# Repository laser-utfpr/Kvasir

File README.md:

# Kvasir

   Dependencies:  
  
   -CMake 3.9

      for Ubuntu: (older version at the packages center atm) get it at: https://cmake.org/download/
      (if you have an older version it's advisable to unistall it first)  

      for Fedora: sudo dnf install cmake

   -OpenCV 2  

      for Ubuntu: sudo apt install libopencv-dev  

      for Fedora: sudo dnf install opencv-devel

   -Boost Libraries  

      for Ubuntu: sudo apt install libboost-all-dev

      for Fedora: sudo dnf install boost-devel

   -Qt5

      for Ubuntu: sudo apt install qttools5-dev

      for Fedora: sudo dnf install qt5-devel-5.11.1-3.fc28.noarch  

	If you want to use gpu, follow this instructions:
		https://www.learnopencv.com/install-opencv3-on-ubuntu/
		https://medium.com/@mengjiunchiou/build-opencv-caffe-with-cuda-9-0-on-ubuntu-16-04-b2794a41612d

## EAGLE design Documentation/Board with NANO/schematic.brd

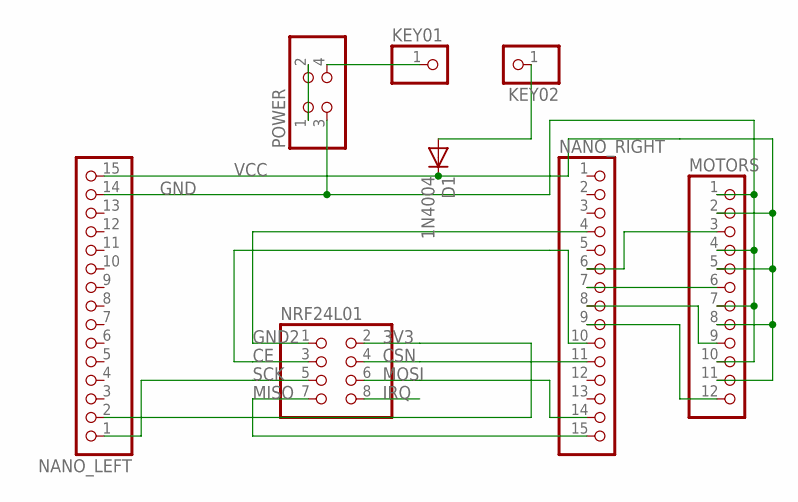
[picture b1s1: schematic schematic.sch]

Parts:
D1: 1N4004; DO41-10
KEY01, KEY02: PINHD-1X1; 1X01
MOTORS: PINHD-1X12; 1X12
NANO_LEFT: PINHD-1X15; 1X15
NANO_RIGHT: PINHD-1X15; 1X15
NRF24L01: PINHD-2X4; 2X04
POWER: PINHD-2X2; 2X02

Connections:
3V3: NANO_LEFT.2, NRF24L01.2
CE: NANO_RIGHT.10, NRF24L01.3
CSN: NANO_RIGHT.11, NRF24L01.4
GND: MOTORS.1, MOTORS.4, MOTORS.7, MOTORS.10, NANO_LEFT.14, POWER.3
GND2: NANO_RIGHT.4, NRF24L01.1
IRQ: NRF24L01.8
MISO: NANO_RIGHT.15, NRF24L01.7
MOSI: NANO_RIGHT.14, NRF24L01.6
unnamed: POWER.1, POWER.2
unnamed: KEY01.1, POWER.4
unnamed: D1.A, KEY02.1
unnamed: MOTORS.12, NANO_RIGHT.9
unnamed: MOTORS.9, NANO_RIGHT.8
unnamed: MOTORS.6, NANO_RIGHT.7
unnamed: MOTORS.3, NANO_RIGHT.6
SCK: NANO_LEFT.1, NRF24L01.5
VCC: D1.C, MOTORS.2, MOTORS.5, MOTORS.8, MOTORS.11, NANO_LEFT.15

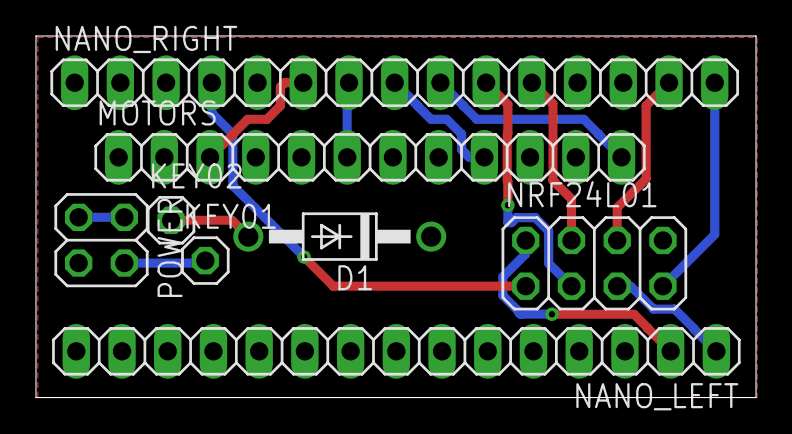
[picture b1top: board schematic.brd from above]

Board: 2 copper layers, 40.0 x 20.1 mm, 8 parts (0 on the bottom side), 16 nets.

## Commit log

2017-08-15 fixed mask opening
2017-08-15 object tracking implemented but not working
2017-08-21 lots of things working
2017-08-21 deleted some junk
2017-08-22 starting to make an interprocesser
2017-08-22 backup
2017-08-28 shared memory crashing often
2017-08-28 shared memory working
2017-08-29 working_with_shared_memory
2017-08-30 vision on cmake, starting obro
2017-08-30 deleting this
2017-08-30 little things
2017-09-05 trying to get obro working
2017-09-06 single shared memory writing, working across processes
2017-09-15 obro progressing
2017-09-18 little progress
2017-09-22 robots 1 and 2, working on 3
2017-09-25 3 robots, right angle ref
2017-09-26 function descriptions for obro
2017-09-26 doing all it needs to do for now
2017-09-27 some comments
2017-10-06 nao sei
2017-10-06 attemp to reorganize stuff
2017-10-06 attempt to reorganize stuff
2017-10-09 something, I don't even know
2017-10-09 some memory leak fix + AI skeleton
2017-10-10 readme dep instructions
2017-10-17 making the ai...
2017-10-19 ai progress?
2017-10-24 we won't back down
2017-10-25 slowly getting there
2017-10-26 now compiling, kbhit in a separate file
2017-10-27 ai progress + some configuring
2017-10-29 readme skipping lines fix
2017-10-30 ai stuff
2017-10-30 leetul
2017-11-01 calculate goalkeeper objective position
2017-11-06 we done?
2017-11-07 little mem leak fix
2017-11-08 kbhit fix, some other stuff
2017-11-08 fixes...
2017-11-08 constants set, no vel on robot 0, save us
2017-11-13 robots semi chasing the ball
2017-11-17 merging with bifrost and freebot
2018-02-05 starting new Kvasirgit checkout Kvasir2 !
2018-02-05 SMMCGUI
2018-02-05 building skeleton
2018-02-05 rebuild
2018-02-08 "qt test project and progress to compiling qt on cmake"
2018-02-15 fk u -fpic! now compiling qt5 with cmake
2018-02-15 now AUTO_MOC and AUTO_UIC are being bitches
2018-02-17 holy guacamole, it's compiling
2018-02-17 compiling with opencv and boost
2018-02-17 CMake 3.9 dependency updated at README
2018-02-19 actually programming now
2018-02-22 progress, using boost serialization now (being a bitch tho)
2018-02-23 boost serialization now included correctly (new boost installation at readme!)
2018-02-23 boost readme
2018-03-01 shared memory progress n keys
2018-03-01 liking signals slots, constructing some sm variables
2018-03-01 ideasNreminders update
2018-03-05 starting to add ai variables
2018-03-05 probaly finished sm variables, added mutex protection
2018-03-06 finishing smmc routines
2018-03-07 paths on settings file, some signals connected
2018-03-12 some initializations and signal to slot connections
2018-03-12 gonna try to use filesystem
2018-03-13 qcoreapplication app exe dir path
2018-03-14 making form
2018-03-14 some parameters changed, ui progress
2018-03-15 game tab finished(!?)
2018-03-19 real ui stuff being implemented
2018-03-19 progress on setting up the ui
2018-03-19 more tasty progress
2018-03-20 typo fix, starting other tabs
2018-03-20 different ally and enemy actions
2018-03-22 updating only on write detection
2018-03-27 vision settings ui
2018-03-27 starting identifiers menus, shutdown fixes
2018-03-28 progress as always
2018-03-29 tags menu and searched region working
2018-04-02 qtTest gone and ui almost finished
2018-04-02 fck forgot ball color (ai settings done tho), making signals
2018-04-03 missing ball button done, missing signals connected
2018-04-03 printing entities?
2018-04-04 printing entities and status
2018-04-04 game control image done (I hope)
2018-04-09 last opencv rectangle thingys
2018-04-10 little bug corrections and commenting
2018-04-10 bug fixes
2018-04-11 boost serialization fix, starting habrok
2018-04-11 makes SMMC read any .sp file
2018-04-12 file stuff, cout and instructions for SMMC
2018-04-16 habrok class
2018-04-17 SMMC without tests, progress in Habrok
2018-04-17 making smmclib
2018-04-18 habrok things
2018-04-18 habrok modeling
2018-04-19 some signal and slot stuff
2018-04-23 starts the image processing
2018-04-24 finds contours
2018-04-24 Habrok should be kinda working with SMMCGUI, but it seg faults
2018-04-25 found seg fault culprits
2018-05-15 just a test bro
2018-05-16 changes sm keys to boost interprocess strings on SMMCGUI
2018-05-16 Habrok opens boost interprocess keys, and working!
2018-05-22 SMMCGUI now compiles with supposedly working boost vectors and strings
2018-05-23 Habrok compiling but not working and giving seg faults
2018-06-12 my signal in your slot
2018-06-19 all habrok signals are not working!
2018-07-11 useless test stuff
2018-07-13 image not in shared memory anymore, commit before qthread adjustments
2018-07-16 making qthread tests
2018-10-12 somehow SMMCGUI threads seem to be working
2018-10-13 image data should be being passed correctly
2018-10-14 image through shared memory working!
2018-10-14 tests deleted
2018-10-14 readme updated for fedora
2018-10-14 Habrok calibration wip
2018-10-15 fedora actually showed a error and some warnings
2018-10-15 habrok contours removed, ui showing
2018-10-15 nothing at all
2018-10-19 habrok ui finished
2018-10-20 color menu working, still needs image menu programming
2018-10-21 image type menu and image displaying
2018-10-22 camera id box
2018-10-23 camera id opening working
2018-10-23 loading camera id at initialization
2018-10-24 makes communication module Vard
2018-10-25 Fixes file loading
2018-10-25 Fixes modules not loading
2018-10-26 scrolls variable accesso 4 lines down, fixing bug
2018-10-26 fixed keys from memory for communication
2018-10-30 part of the changes to match kvasir2 commit
2018-10-30 fixing commit
2018-10-30 fixing commit.
2018-10-30 fixing commit..
2018-10-30 fixing commit...
2018-10-31 fixes habrok calibration loading, starting robot recognizer
2018-11-01 finding ball, other entities wip
2018-11-02 finds robot1
2018-11-02 moar things on calibration, robot4
2018-11-03 habrok should be done o/
2018-11-03 slight aesthetic fix
2018-11-03 fix for opencv3.0
2018-11-03 starting vor
2018-11-03 some bugs fixes, vor communicating, strategy wip
2018-11-04 turbo -O3 compiling
2018-11-04 not tested and missing stuff but should have a simple playing capability
2018-11-05 slight fix, -O3 breaks things in some PCs
2018-11-06 fixes
2018-11-08 removed some pointers
2018-11-09 things
2018-12-18 stopped the use of unnecessary pointers
2018-12-18 reused some pointers, because without them the motor doesn't answer correctly
2019-01-22 start documentation
2019-01-22 start Vard documentation
2019-01-23 finished vard documentation
2019-01-24 Include hardware documentation
2019-02-12 updated class diagrams
2019-02-12 update class diagrams
2019-02-13 made Habrok class diagram, start the SMMCGUI one
2019-02-14 fineshed class diagrams
2019-02-15 started the new vard program
2019-02-16 finished the new vard version
2019-02-18 fixed the file problems
2019-02-18 set the flag XBEE if a xbee will be use
2019-02-18 remove print
2019-02-18 add the xbee file settings
2019-02-18 add the freebot program with xbee to be modular after
2019-02-18 exit vard if there isn't serial communication
2019-02-19 start the manual commands model
2019-02-20 made the manual control menu, and the action of de manual controls
2019-02-21 finished the manual control sender
2019-02-21 try to send stop in the manual control
2019-02-22 finished the manual control
2019-02-22 fixed nan comparisons
2019-02-22 commented prints in the principals loops
2019-02-22 made the new freebot class diagram version
2019-02-25 made the new freebot version
2019-02-25 there's a problem with the vard sending address
2019-02-26 fixed the wrong address
2019-02-26 feixed some communication errors
2019-02-26 made more tests, manual control is not working well
2019-02-27 fixed some errors, know there ins't delat
2019-02-27 know there ins't delay
2019-02-27 update transmitter program
2019-02-28 changed the main window to be resized without lost the icons from screen
2019-03-01 resize game control image to avoid problems
2019-03-07 changed scaling politic
2019-03-07 add button information to mark the motor one
2019-03-08 fixed the directions
2019-03-08 show the information of all robots if need
2019-03-11 try to improve the transmitter to avoid crash
2019-03-12 fixed some problems
2019-03-12 start the movestraight function
2019-03-13 fixed the manual control
2019-03-13 fixed the angle compare
2019-03-13 started the goalkeeper strateg
2019-03-14 try to optimize the goalkeeper strategy
2019-03-18 improve the goalkeeper strategy
2019-03-19 improve the defender startegy
2019-03-19 improve the attacker strategy
2019-03-19 testing
2019-03-29 added script to run the SMMCGUI
2019-03-30 improve the script
2019-04-02 create new file
2019-04-02 removed file
2019-04-02 new file
2019-04-02 file has been deleted
2019-04-17 fixed the problem with the robots receiving wrong messages
2019-04-17 fixed the script to directories with space
2019-04-18 improve the assign role
2019-04-23 Fixed robot destination
2019-04-24 started the gpu use
2019-04-24 made the threshold operation with gpu
2019-04-24 try to use HoughCircles
2019-04-24 comment
2019-04-25 try to use erode and dilate functions
2019-04-29 started the gpu use in guis
2019-04-29 try to do configuration, but something don't work properly
2019-04-30 know max value change image
2019-04-30 fixed robot destintion to the limit of the field in manual control
2019-05-02 Fixed robot destination in manual control
2019-05-03 Fixed robot destination to all directions
2019-05-06 something
2019-05-07 start the use of HoughCircles on habrok gui
2019-05-07 finished the tests with HoughCircles, the findContours is almost 5x more fast
2019-05-07 Added previous_destination
2019-05-07 Fixed destination to ball
2019-05-07 reduced the image size
2019-05-08 improve the script to do rebuild
2019-05-08 add offsets to the attacker and goalkeeper players
2019-05-08 clear rad key for Vard
2019-05-09 Fixed Vor constants
2019-05-09 Fixed Right side
2019-05-09 started the side menu
2019-05-09 started the gui menu side
2019-05-10 fineshed the side menu
2019-05-10 add previous calibration to fast setup
2019-05-13 Fixed spin to both sides
2019-05-28 Add strategyPON
2019-06-05 started the PON rules
2019-06-05 added previous fbe controler
2019-06-13 added relevance files to pon development
2019-06-18 try to compile de pon program
2019-06-18 made more tests
2019-06-25 Added Robot.nop
2019-08-08 Robot.nop compilation succeeded
2019-08-30 Generated files
2019-08-30 Generated PON files
2019-09-02 Added strategy.nop
2019-09-03 Minor improvements in strategy.nop
2019-09-09 Implemented basic rules
2019-09-29 added undef because gpu
2019-09-29 removed queue
2019-10-07 Tested APF
2019-10-08 APF test working
2019-10-08 Tested APF for ally
2019-10-11 Tested APF with attacker
2019-10-12 Improved strategy for the attacker
2019-10-12 Improved attacker strategy
2019-10-12 Fixed manual control
2019-10-18 Improved Support and Defender strategies.
2019-10-18 Improved Penalty and Kickoffs strategies
2019-10-23 Robocup tests
2019-10-24 Robocup tests 2.0
2019-10-24 somethong
2019-10-24 fixed somethings
2019-10-24 blabla
2019-10-24 Changed attacker strategy when defending
2019-10-24 nothing
2020-02-05 Final Version of the competition
